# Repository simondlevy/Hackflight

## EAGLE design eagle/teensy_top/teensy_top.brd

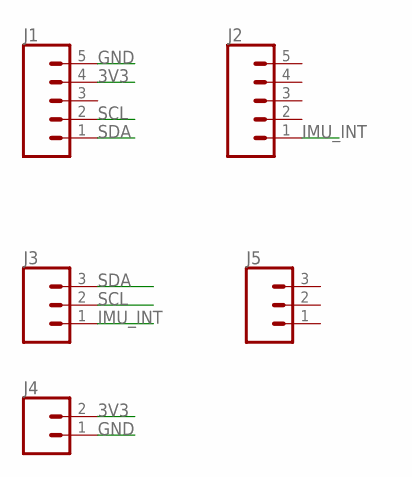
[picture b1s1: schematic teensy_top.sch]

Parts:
J1, J2: CONN_05NO_SILK; 1X05_NO_SILK
J3, J5: CONN_031X03_NO_SILK; 1X03_NO_SILK
J4: CONN_021X02_NO_SILK; 1X02_NO_SILK

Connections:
3V3: J1.4, J4.2
GND: J1.5, J4.1
IMU_INT: J2.1, J3.1
SCL: J1.2, J3.2
SDA: J1.1, J3.3

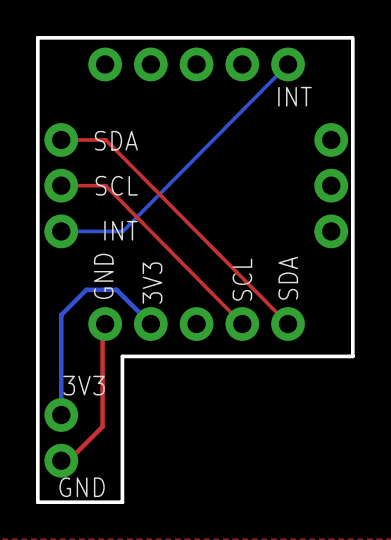
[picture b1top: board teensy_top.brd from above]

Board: 2 copper layers, 17.5 x 25.8 mm, 5 parts (0 on the bottom side), 5 nets.

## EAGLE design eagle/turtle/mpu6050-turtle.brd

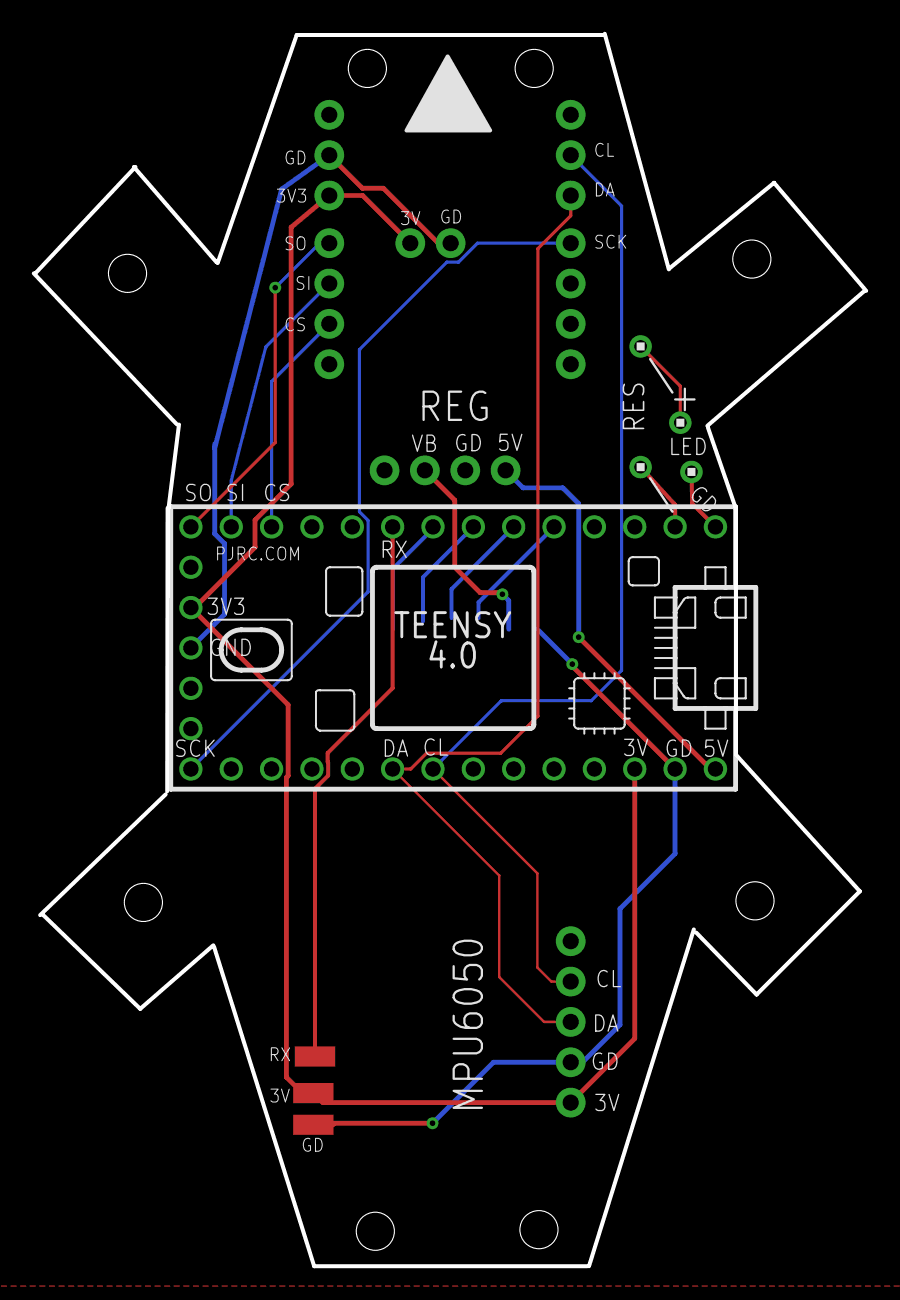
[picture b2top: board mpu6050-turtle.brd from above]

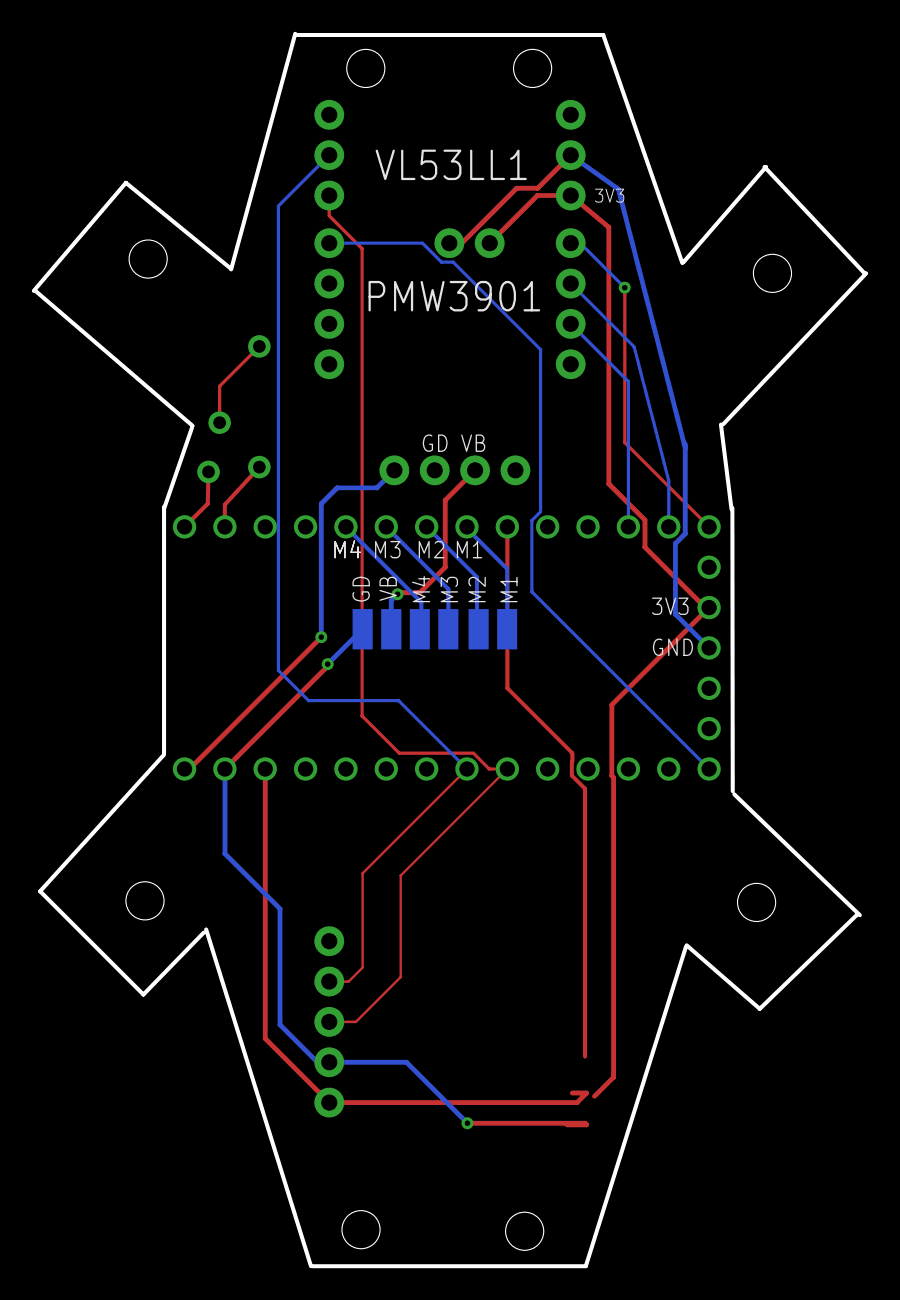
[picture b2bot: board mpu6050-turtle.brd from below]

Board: 2 copper layers, 52.4 x 77.6 mm, 21 parts (6 on the bottom side), 18 nets.

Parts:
3V: SMD1,27-2,54
GD: SMD1,27-2,54
GND: SMD1,27-2,54
J1: 1X05_NO_SILK
M1, M2, M3, M4: SMD1,27-2,54
PMW1, PMW2: 1X04_NO_SILK
PMW3: 1X02_NO_SILK
REG: 1X04_NO_SILK
RX: SMD1,27-2,54
U$1: TEENSY_4.0
U$3, U$4, U$6, U$7: 1X1
VBAT: SMD1,27-2,54
VL1, VL2: 1X03_NO_SILK

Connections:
3V3: 3V.1, J1.1, PMW3.1, U$1.3V3_LN, U$1.3V3_LO, VL2.1
5V: REG.1, U$1.VIN
CS: PMW2.3, U$1.10/CS
G2: U$1.GND, U$7.1
GND: GD.1, GND.1, J1.2, PMW3.2, REG.2, U$1.GND2, U$1.GND3, VL2.2
LED_R_IN: U$1.0/RX, U$3.1
LED_R_OUT: U$4.1, U$6.1
M1: M1.1, U$1.6
M2: M2.1, U$1.5
M3: M3.1, U$1.4/CANRX
M4: M4.1, U$1.3/CANTX
MISO: PMW2.1, U$1.12/MISO
MOSI: PMW2.2, U$1.11/MOSI
RX: RX.1, U$1.7
SCK: PMW1.1, U$1.13/SCK
SCL: J1.4, U$1.19/A5/SCL, VL1.2
SDA: J1.3, U$1.18/A4/SDA, VL1.1
VBAT: REG.3, VBAT.1

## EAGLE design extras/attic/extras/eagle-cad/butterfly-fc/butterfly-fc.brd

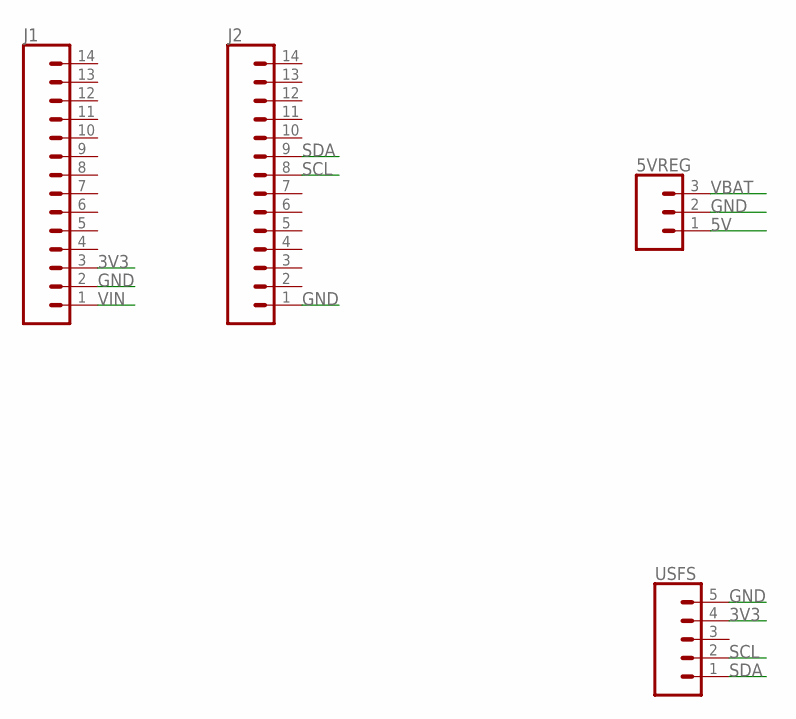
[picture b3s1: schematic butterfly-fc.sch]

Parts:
5VREG: CONN_031X03_NO_SILK; 1X03_NO_SILK
J1, J2: CONN_14NO_SILK; 1X14_NO_SILK
USFS: CONN_05NO_SILK; 1X05_NO_SILK

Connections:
3V3: J1.3, USFS.4
5V: 5VREG.1
GND: 5VREG.2, J1.2, J2.1, USFS.5
SCL: J2.8, USFS.2
SDA: J2.9, USFS.1
VBAT: 5VREG.3
VIN: J1.1

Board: 2 copper layers, 4 parts (0 on the bottom side), 4 nets, no tracks yet.

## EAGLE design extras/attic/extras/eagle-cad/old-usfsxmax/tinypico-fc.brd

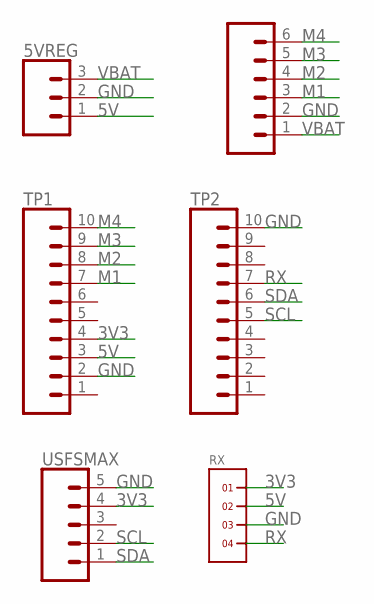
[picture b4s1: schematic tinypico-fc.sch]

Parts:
5VREG: CONN_031X03_NO_SILK; 1X03_NO_SILK
ESC: CONN_06NO_SILK_FEMALE_PTH; 1X06_NO_SILK
RX: 1X4
TP1, TP2: CONN_10NO_SILK_PTH_FEMALE; 1X10_NO_SILK
USFSMAX: CONN_05NO_SILK; 1X05_NO_SILK

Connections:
3V3: RX.1, TP1.4, USFSMAX.4
5V: 5VREG.1, RX.2, TP1.3
GND: 5VREG.2, ESC.2, RX.3, TP1.2, TP2.10, USFSMAX.5
M1: ESC.3, TP1.7
M2: ESC.4, TP1.8
M3: ESC.5, TP1.9
M4: ESC.6, TP1.10
RX: RX.4, TP2.7
SCL: TP2.5, USFSMAX.2
SDA: TP2.6, USFSMAX.1
VBAT: 5VREG.3, ESC.1

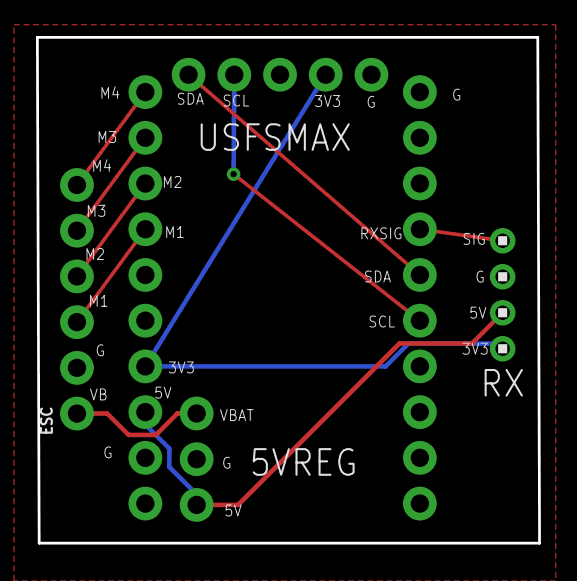
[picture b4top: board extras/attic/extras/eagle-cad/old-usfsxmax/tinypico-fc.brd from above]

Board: 2 copper layers, 27.9 x 28.1 mm, 6 parts (0 on the bottom side), 11 nets.

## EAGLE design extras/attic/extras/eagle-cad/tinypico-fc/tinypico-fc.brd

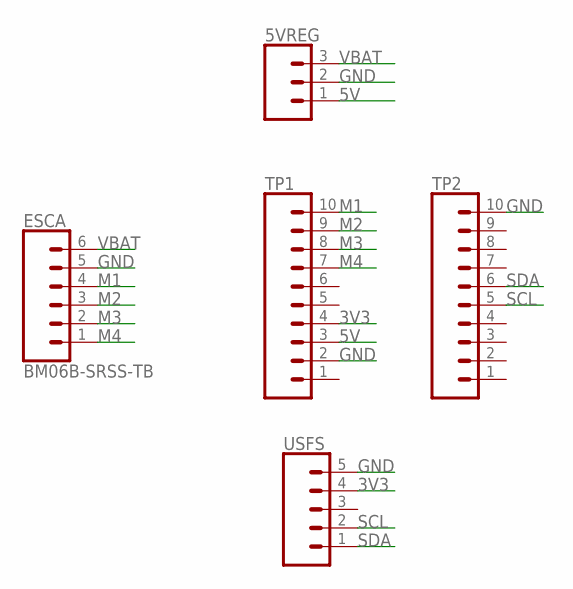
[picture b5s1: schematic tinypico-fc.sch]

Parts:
5VREG: CONN_031X03_NO_SILK; 1X03_NO_SILK
ESC: BM06B-SRSS-TB; JST-6-SMD-HORI-1.0MM
TP1, TP2: CONN_10NO_SILK_PTH_FEMALE; 1X10_NO_SILK
USFS: CONN_05NO_SILK; 1X05_NO_SILK

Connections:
3V3: TP1.4, USFS.4
5V: 5VREG.1, TP1.3
GND: 5VREG.2, ESC.5, TP1.2, TP2.10, USFS.5
M1: ESC.4, TP1.10
M2: ESC.3, TP1.9
M3: ESC.2, TP1.8
M4: ESC.1, TP1.7
SCL: TP2.5, USFS.2
SDA: TP2.6, USFS.1
VBAT: 5VREG.3, ESC.6

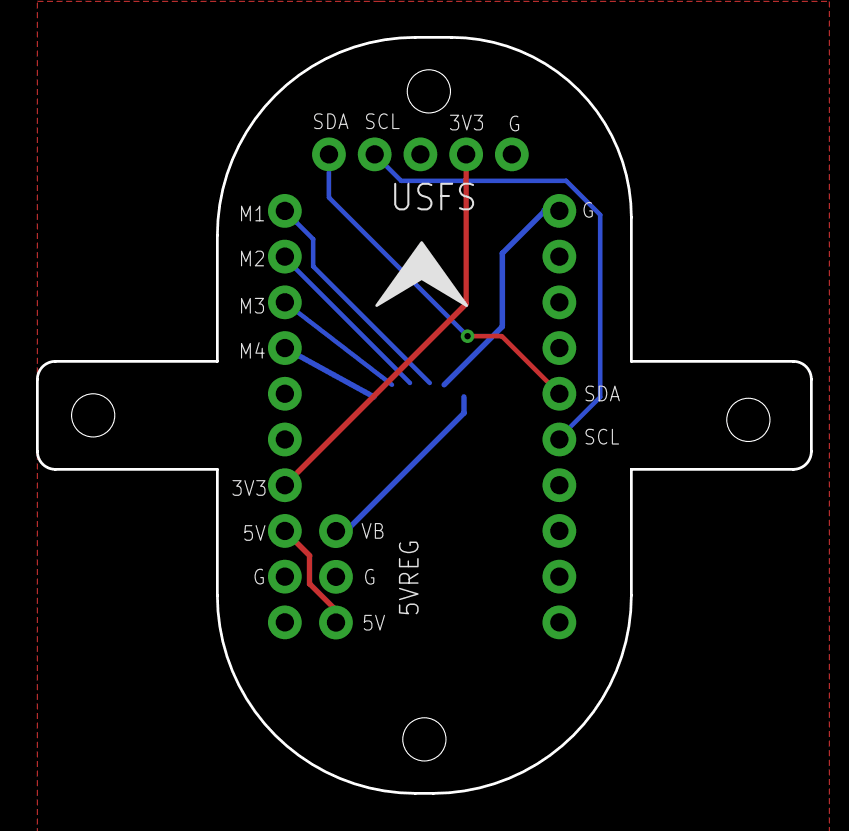
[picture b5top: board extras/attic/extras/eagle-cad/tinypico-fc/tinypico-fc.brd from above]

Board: 2 copper layers, 43.0 x 42.0 mm, 5 parts (1 on the bottom side), 10 nets.

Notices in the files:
parts and their libraries:
SparkFun-Connectors: Licensing: Creative Commons ShareAlike 4.0 International - https://creativecommons.org/licenses/by-sa/4.0
